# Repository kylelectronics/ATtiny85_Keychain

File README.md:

# Lighted Keychain
[madewith](https://img.shields.io/badge/made%20with-KiCad-blue)

ATtiny85-based illuminated PCB keychain featuring an organization symbol.

## Description
Originally developed for Ruddock House of Caltech, this repo contains modified files featuring the flame logo of Sparkfun Electronics.

This is a 1.6" by 1.9" PCB keychain featuring an organization crest on the top copper, based on [https://github.com/ElectronicToast/ruddblink]. A ring of 8 LEDs around the crest is controlled by an ATtiny85 through a 74HC595 shift register. This keychain is intended to be compact and aesthetic, but also simple to hand solder; all packages are SOIC and 0805 or larger.

The keychain is powered by a CR2032 coin cell through the coin cell holder footprint on the back, or through an alternative power source (2.7-5.5V) soldered to those pads.

## Features
- ATtiny85 in SOIC-8 package driving 74HC595 shift register in SOIC-16 package
- PWM-able output
- Power switch
- User pushbutton
- MOSFET polarity protection
- PTC fuse
- No through hole components

## Notes

No input voltage regulation is present. Do not apply more than 5.5 V, the maximum voltage for the ATtiny.

This PCB is designed with KiCad EDA 5.1.6. Schematic and board files may be found under `/attiny85-keychain`, with documentation under `/attiny85-keychain/doc`.

## Author
- Kyle Piper - Undergraduate, Mechanical Engineering, Caltech Class of 2024
- Original design by Ray Sun, Electrical Engineering, Caltech Class of 2020

## License
<br />Unless otherwise noted, this schematic and PCB design, with associated symbol and footprint files, are licensed under a <a rel="license" href="http://creativecommons.org/licenses/by-sa/4.0/">Creative Commons Attribution-ShareAlike 4.0 International License</a>. Flame logo is property of Sparkfun Electronics.

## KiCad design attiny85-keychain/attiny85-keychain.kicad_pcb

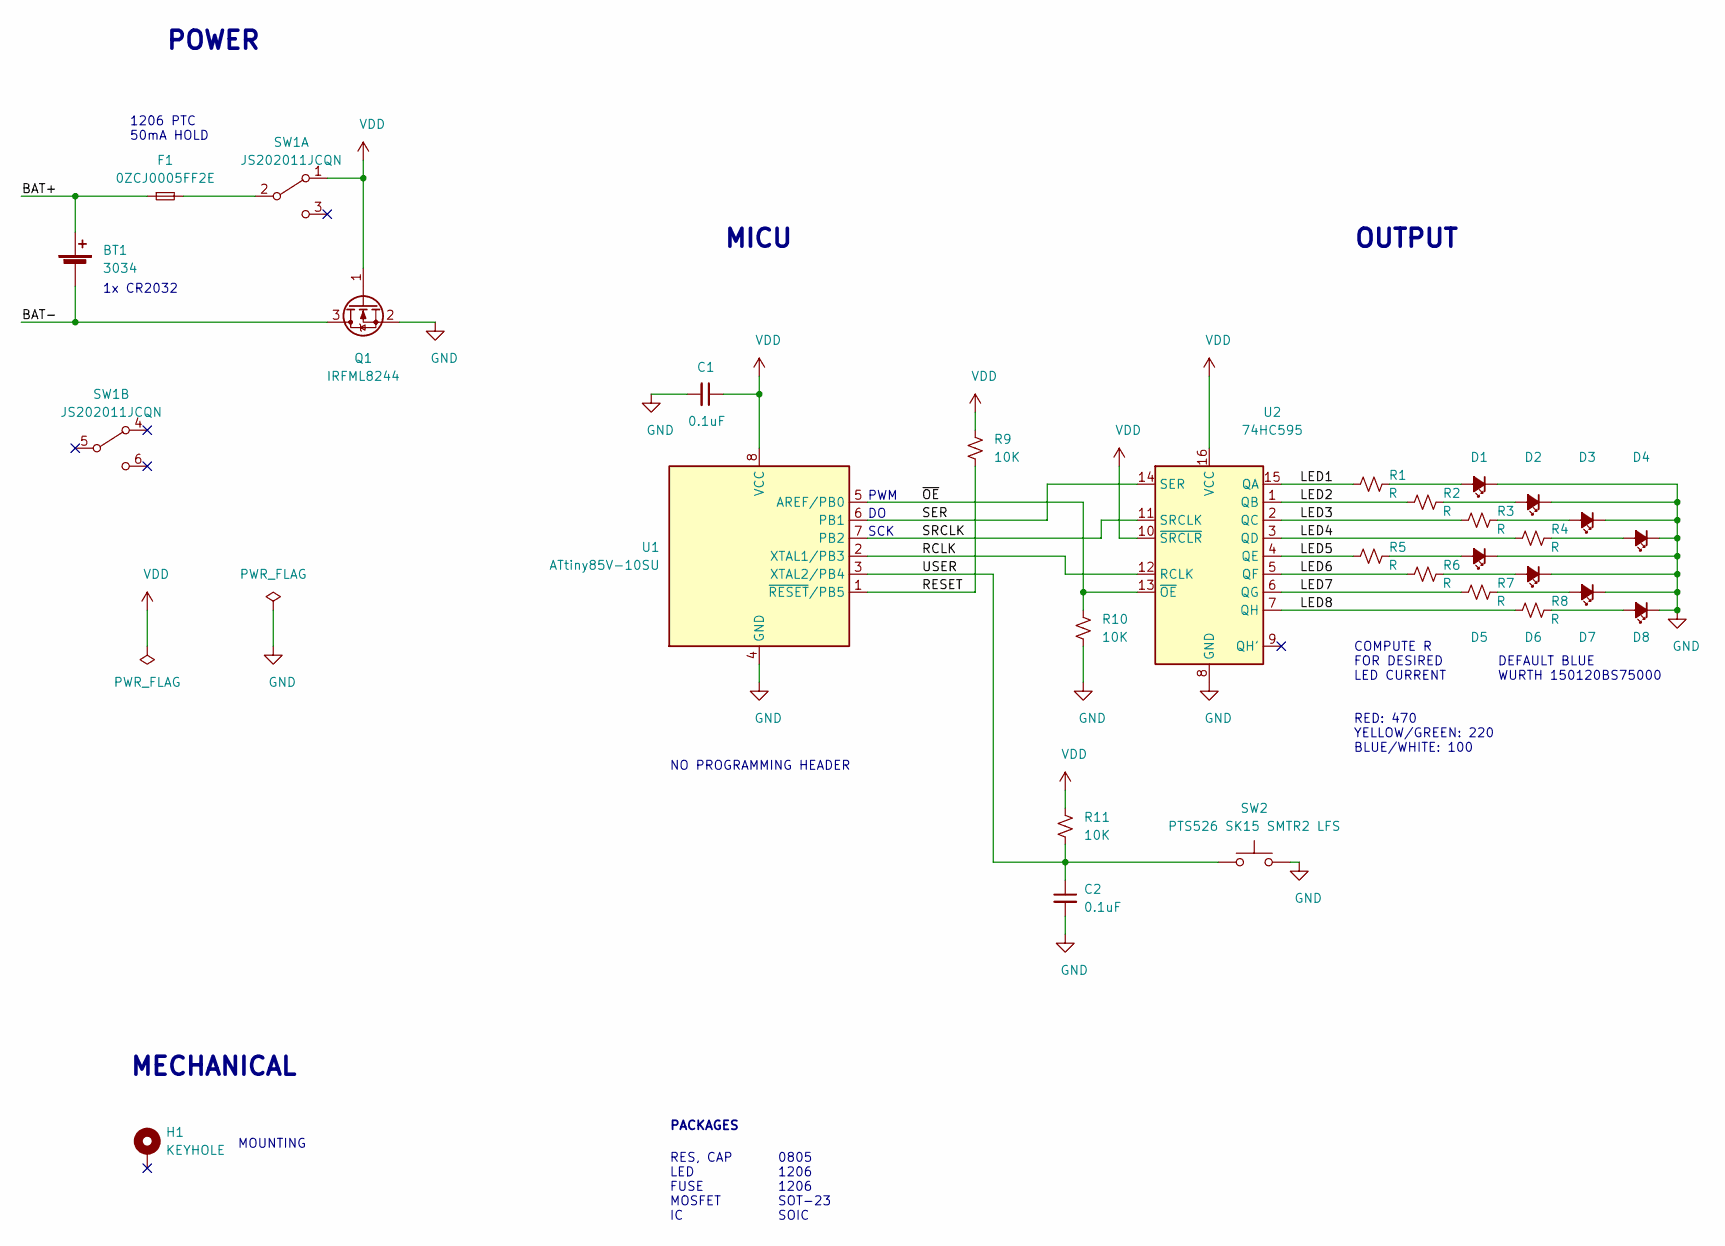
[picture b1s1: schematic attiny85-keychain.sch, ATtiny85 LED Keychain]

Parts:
BT1: 3034; BatteryHolder_Keystone_3034_Wide
C1, C2: 0.1uF; C_0805_2012Metric_Pad1.15x1.40mm_HandSolder
D1, D2, D3, D4, D5, D6, D7, D8: 150120BS75000; LED_1206_Uniform_HandSolder
F1: 0ZCJ0005FF2E; Fuse_1206_3216Metric_Pad1.42x1.75mm_HandSolder
H1: KEYHOLE; MountingHole_Keyring
Q1: IRFML8244; SOT-23_Handsoldering
R1, R2, R3, R4, R5, R6, R7, R8: R; R_0805_2012Metric_Pad1.15x1.40mm_HandSolder
R9, R10, R11: 10K; R_0805_2012Metric_Pad1.15x1.40mm_HandSolder
SW1: JS202011JCQN; SW_SPDT_CK-JS202011JCQN
SW2: PTS526 SK15 SMTR2 LFS; SW_Push_PTS526
U1: ATtiny85V-10SU; SOIJ-8_5.3x5.3mm_P1.27mm
U2: 74HC595; SOIC-16_3.9x9.9mm_P1.27mm

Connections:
/BAT+: BT1.1 (+), F1.1
/BAT-: BT1.2 (-), Q1.3 (D)
/LED1: R1.1, U2.15 (QA)
/LED2: R2.1, U2.1 (QB)
/LED3: R3.1, U2.2 (QC)
/LED4: R4.1, U2.3 (QD)
/LED5: R5.1, U2.4 (QE)
/LED6: R6.1, U2.5 (QF)
/LED7: R7.1, U2.6 (QG)
/LED8: R8.1, U2.7 (QH)
/RCLK: U1.2 (XTAL1/PB3), U2.12 (RCLK)
/RESET: R9.2, U1.1 (~RESET~/PB5)
/SER: U1.6 (PB1), U2.14 (SER)
/SRCLK: U1.7 (PB2), U2.11 (SRCLK)
/USER: C2.1, R11.2, SW2.1, U1.3 (XTAL2/PB4)
/~OE: R10.1, U1.5 (AREF/PB0), U2.13 (~OE)
GND: C1.2, C2.2, D1.1 (K), D2.1 (K), D3.1 (K), D4.1 (K), D5.1 (K), D6.1 (K), D7.1 (K), D8.1 (K), Q1.2 (S), R10.2, SW2.2, U1.4 (GND), U2.8 (GND)
unnamed: D1.2 (A), R1.2
unnamed: D2.2 (A), R2.2
unnamed: D3.2 (A), R3.2
unnamed: D4.2 (A), R4.2
unnamed: D5.2 (A), R5.2
unnamed: D6.2 (A), R6.2
unnamed: D7.2 (A), R7.2
unnamed: D8.2 (A), R8.2
unnamed: F1.2, SW1.2 (B)
VDD: C1.1, Q1.1 (G), R9.1, R11.1, SW1.1 (A), U1.8 (VCC), U2.10 (~SRCLR), U2.16 (VCC)

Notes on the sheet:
NO PROGRAMMING HEADER
POWER
MICU
OUTPUT
SCK
DEFAULT BLUE WURTH 150120BS75000
MOUNTING
MECHANICAL
COMPUTE R FOR DESIRED LED CURRENT
PACKAGES
RES, CAP LED FUSE MOSFET IC
0805 1206 1206 SOT-23 SOIC
1x CR2032
1206 PTC 50mA HOLD
RED: 470 YELLOW/GREEN: 220 BLUE/WHITE: 100
PWM

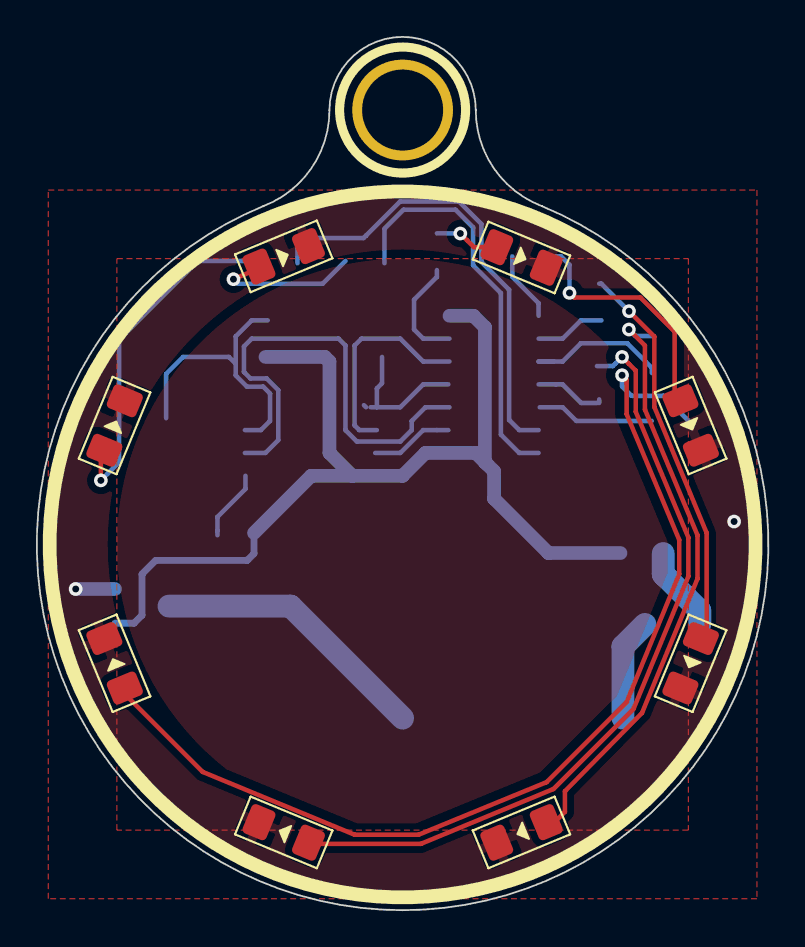
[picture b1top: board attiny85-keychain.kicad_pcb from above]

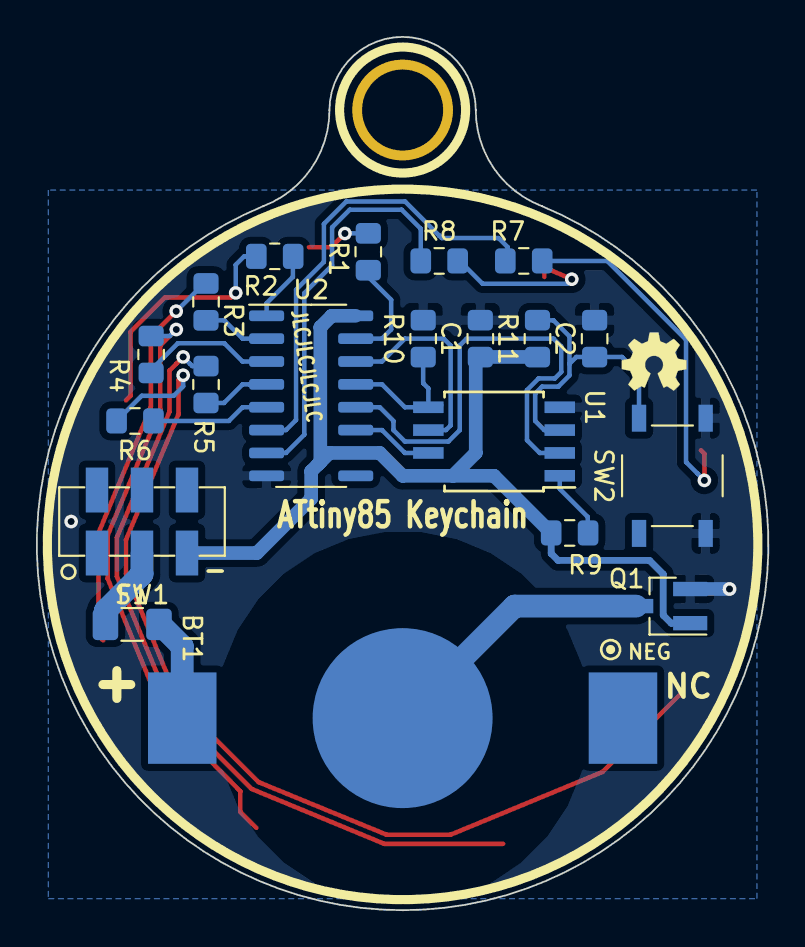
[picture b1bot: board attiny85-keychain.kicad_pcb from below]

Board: 2 copper layers, 40.6 x 48.5 mm, 29 parts (20 on the bottom side), 27 nets.

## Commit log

2019-07-05 Make KiCad project
2019-07-05 Start design
2019-07-07 Add old PCB library
2019-07-07 Continue design
2019-07-07 Move files
2019-07-17 Choose polarity protection MOSFET
2019-07-21 Select battery holder and switches
2019-07-21 Replace resistor packs with discrete resistors
2019-07-21 Select fuse
2019-07-22 Definitely not driving 8 blue LEDs off single CR2032
2019-07-22 Add symbols for mounting hole and crest copper
2019-07-22 Add labels to MCU pins
2019-07-22 Replace MOSFET with SOT-23 for easier soldering
2019-07-23 Design for 2 3V cells in series
2019-07-25 Replace LDO
2019-07-25 Remove LICENSE
2019-07-25 Add LICENSE
2019-07-30 Add pulldown to ~OE
2019-08-05 Begin layout
2019-08-07 Remove dual cell and JST option, continue design
2019-08-08 Update power switch
2019-08-09 Continue placement
2019-08-10 Finish placement
2019-08-12 Rename project
2019-08-12 Update licensing
2019-08-12 Add mounting hole footprint
2019-08-12 Begin routing
2019-08-12 Rename pushbutton footprint
2019-08-14 Remove unnecessary crest copper pad component
2019-08-14 Did most routing
2019-08-15 Fix footprint courtyard
2019-08-15 Pass ERC
2019-08-15 Finish routing
2019-08-15 Position designators
2019-08-16 Add soldermask crest with appropriate scale
2019-08-16 Remove silkscreen
2019-08-16 Update footprint path
2019-08-16 Finish board design
2019-08-16 Fix some designator positioning
2019-08-16 Add dimensions
2019-08-17 Add soldermask clearance into footprint itself
2019-08-17 Create symmetric 1206 LED footprint
2019-08-17 Adjust some positions and shrink soldermask clearance
2019-08-17 Reposition some designators
2019-08-17 Vanity edits
2019-08-17 Shrink negative pad mask clearance to avoid DRC complaint
2019-08-17 Remove target and edit dimension drawings
2019-08-17 Add OSHW symbol
2019-08-18 Migrate to KiCad 5.1.4 and tidy up
2019-08-18 Additional cosmetic edits
2019-08-18 Move footprint directory
2019-08-18 Fix some DFM issues
2019-08-19 More cosmetic edits
2019-08-19 Move dimension marker
2019-08-19 Fix vertical dimension mark
2019-08-19 Make pushbutton pads slightly wider
2019-08-20 Add top pour to keyhole neck
2019-08-20 Clean up dimension drawings
2019-08-20 Remove neck zone
2019-08-21 Generate BOM
2019-08-24 Propose alternative pinout for USI shift register write control
2019-08-24 Update schematic
2019-08-26 Make logo smaller
2019-08-26 Move additional traces for cosmetics
2019-08-26 Generate fabrication prints
2019-08-26 Generate gerbers for prototype production
2019-09-17 Versioning for production version
2019-09-17 Replace ATtiny85-20SU with ATtiny85V-10SU for more usable battery capacity
2019-09-17 Change reference C3 to C2
2019-10-31 Generate Gerbers for production
2019-10-31 Update BOM
2019-10-31 Generate fabrication documentation for release
2019-12-06 Fix front fab print
2019-12-30 Generate Gerbers for fabrication without JLCPCB serial number
2020-02-06 Generate stencil PDFs
2020-02-12 Neck down MOSFET drain trace
